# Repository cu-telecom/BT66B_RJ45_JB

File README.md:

# BT66B_RJ45_JB

A PCB to breakout 4 Telephone lines on a single RJ45 to 4 lines on individual lines.

Designed to mount into a BT66B Junction Box.

This is currently untested

## License

- This project is licensed under the MIT license

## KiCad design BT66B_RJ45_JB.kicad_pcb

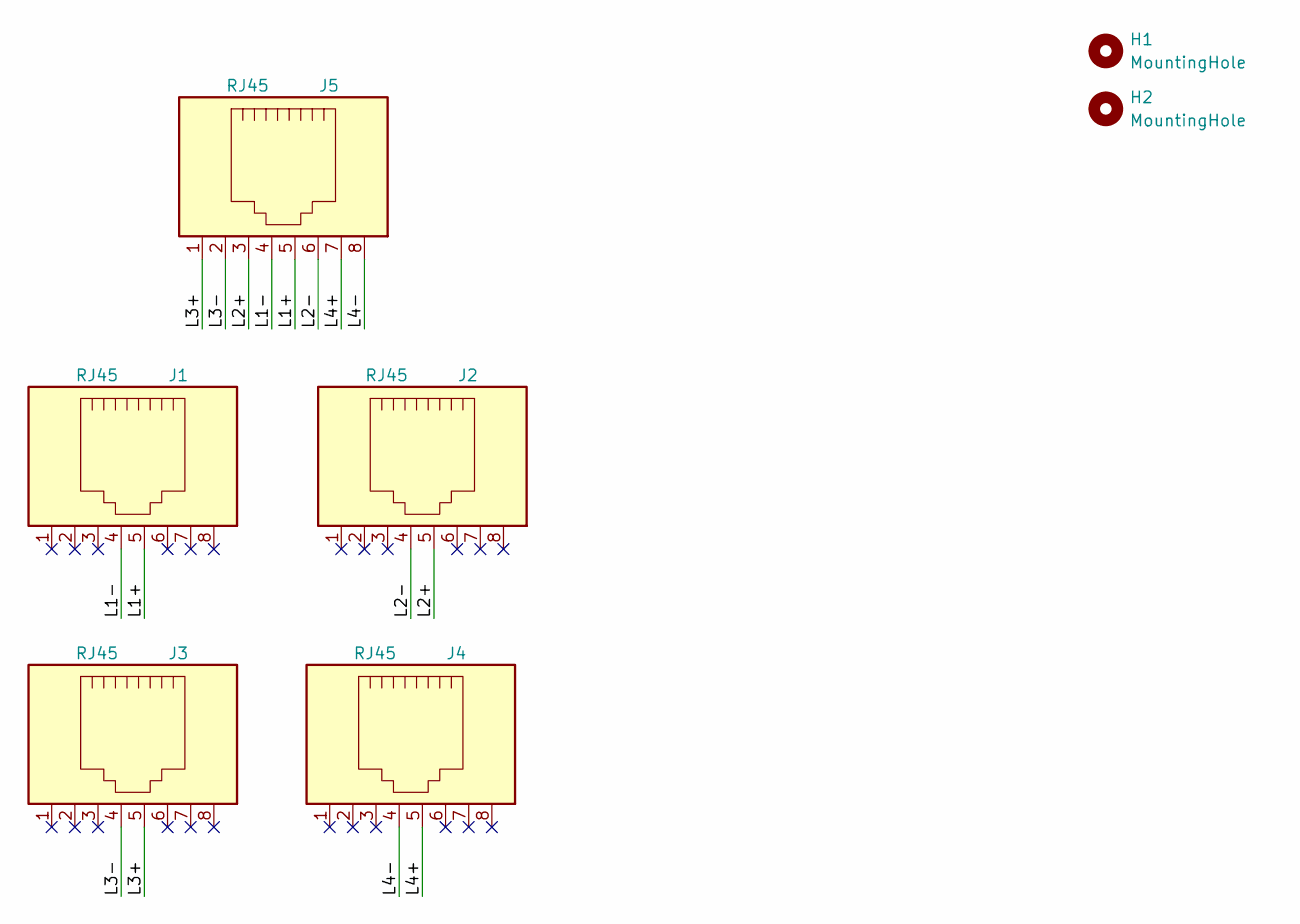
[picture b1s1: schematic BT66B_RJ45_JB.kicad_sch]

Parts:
H1, H2: MountingHole; MountingHole_4mm
J1, J2, J3, J4, J5: RJ45

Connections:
/L1+: J1.5, J5.5
/L1-: J1.4, J5.4
/L2+: J2.5, J5.3
/L2-: J2.4, J5.6
/L3+: J3.5, J5.1
/L3-: J3.4, J5.2
/L4+: J4.5, J5.7
/L4-: J4.4, J5.8

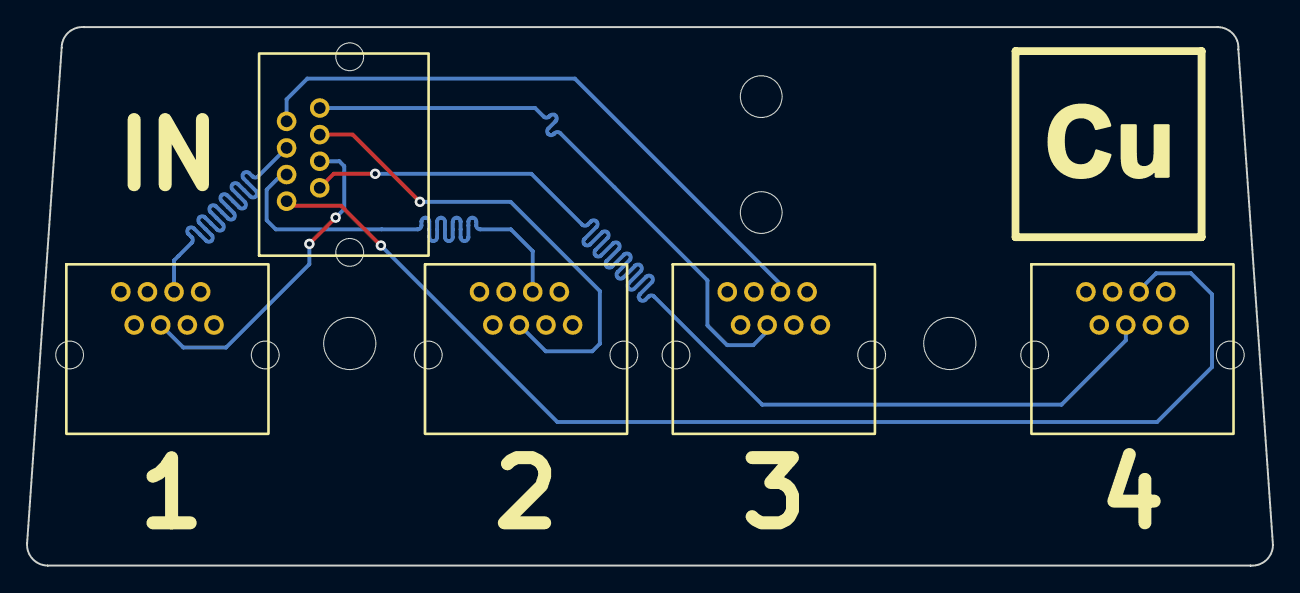
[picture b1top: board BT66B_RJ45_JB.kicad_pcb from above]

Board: 2 copper layers, 95.5 x 41.3 mm, 7 parts (0 on the bottom side), 8 nets.

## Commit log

2024-03-01 init
2024-03-01 Add Gerbers
2025-03-01 Latest changes
